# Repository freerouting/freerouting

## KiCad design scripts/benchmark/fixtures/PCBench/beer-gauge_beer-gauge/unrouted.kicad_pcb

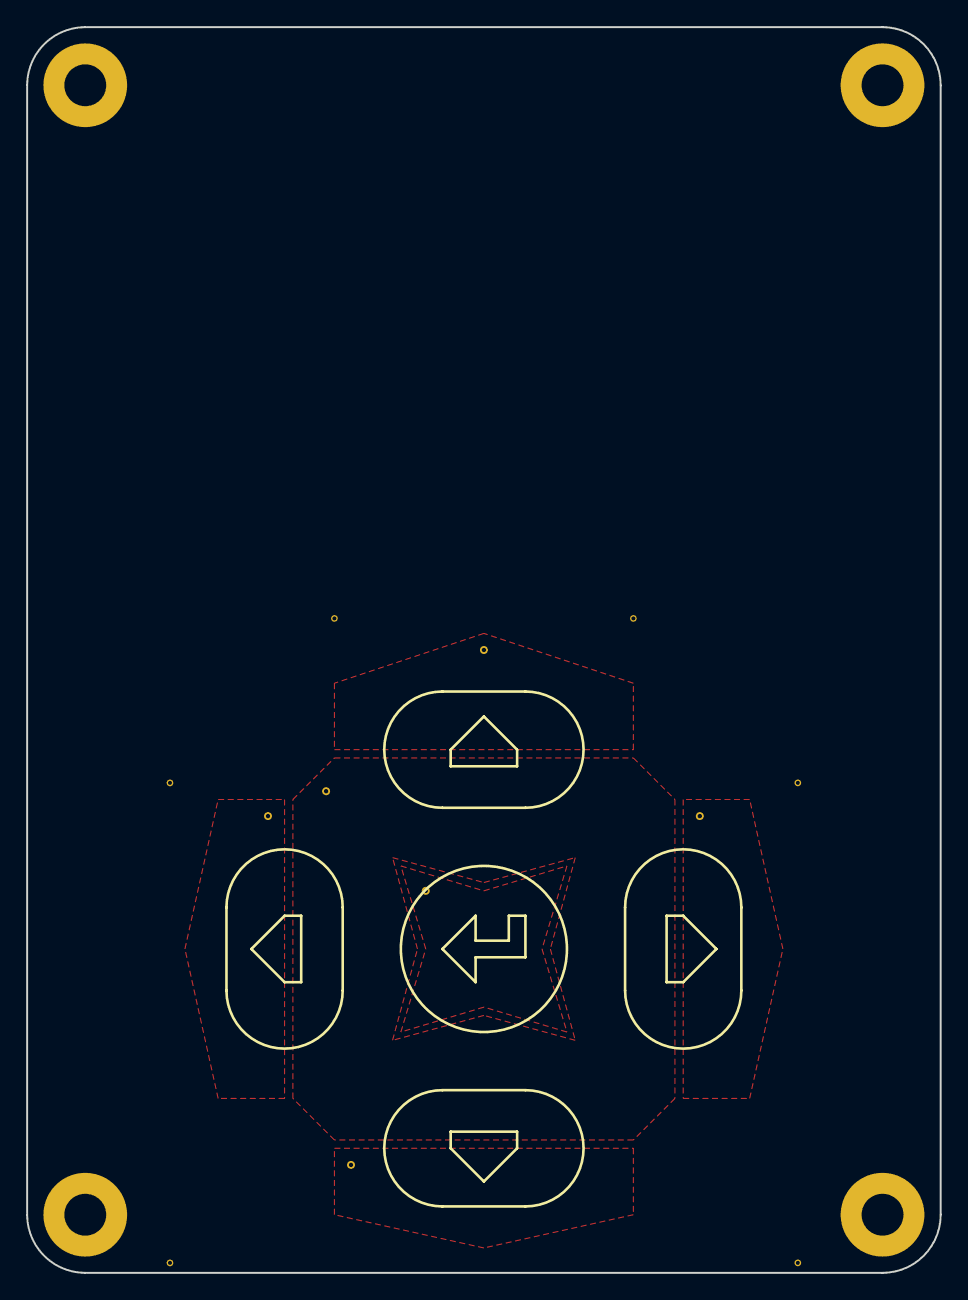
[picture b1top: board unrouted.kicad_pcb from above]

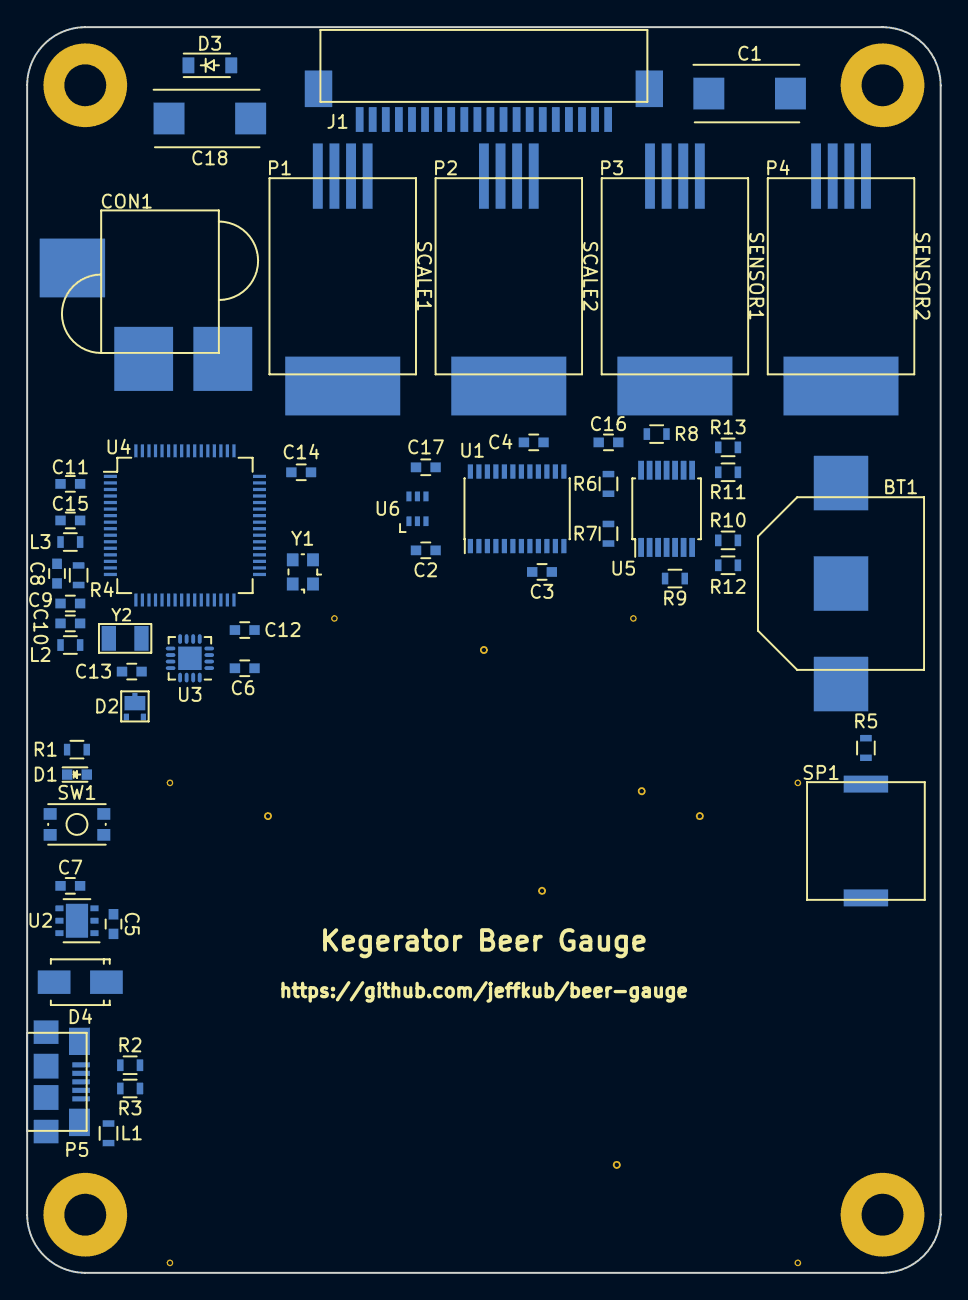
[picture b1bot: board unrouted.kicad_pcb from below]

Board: 4 copper layers, 69.8 x 95.2 mm, 62 parts (56 on the bottom side), 64 nets, no tracks yet.

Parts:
BT1: Battery; BK-885
C1: 220u; TantalC_SizeD_EIA-7343_Reflow
C2, C3, C4, C6, C9, C10, C11, C12, C13, C14, C16, C17: 0.1u; C_0603
C5, C7, C8, C15: 2.2u; C_0603
C18: 100u; TantalC_SizeD_EIA-7343_Reflow
CON1: BARREL_JACK; PJ-070AH-SMT
D1: LED; LED_0603
D2: PMEG4010CPA; SOT1061
D3: DDZ6V2B; SOD-123
D4: S1B; SMA_Standard
J1: OLED_MODULE; 0522712069
L1, L3: 600 Ohm/100 MHz; R_0603
L2: 600 Ohm/100 Mhz; R_0603
P1, P2, P3, P4: CONN_01X04; 0855135016
P5: USB_OTG; 10118192
R1, R4, R5: 470; R_0603
R2, R3: 33; R_0603
R6, R7, R8, R9, R10, R11, R12, R13: 4.7k; R_0603
SP1: PIEZO; PKMCS
SW1: SW_PUSH; SW_SPST_KMR2
U1: ADS1232; TSSOP-24_4.4x7.8mm_Pitch0.65mm
U2: LP38691; DFN-6-1EP_3x3mm_Pitch0.95mm
U3: MKL02Z32; QFN-16-1EP_3x3mm_Pitch0.5mm
U4: MK20DX256VLH7; LQFP-64_10x10mm_Pitch0.5mm
U5: TCA9543A; TSSOP-14_4.4x5mm_Pitch0.65mm
U6: SN74LVC1G58; SC-70-6
W1, W2, W3, W4, W5, W6: TEST_1P; PadVia
Y1: 16 MHz; Crystal_SMD_2520_4Pads
Y2: 32.768 kHz; ABS07

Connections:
+3V3: C1.1, C2.1, C6.1, C7.1, C11.1, C12.1, C14.1, C15.1, C16.1, C17.1, D2.2, J1.2, L3.1, R6.1, R7.1, R8.1, R9.1, R10.1, R11.1, R12.1, R13.1, U1.1, U2.4, U2.5, U3.1, U4.3, U4.7, U4.30, U4.48, U5.14, U6.5
+5V: C4.1, C5.1, C18.1, CON1.1, D3.1, D4.1, P1.1, P2.1, P3.1, P4.1, U1.16, U1.18, U2.1, U2.6
/Teensy/0: U1.19, U4.39
/Teensy/1: U1.20, U4.40
/Teensy/2: U1.22, U4.57
/Teensy/3: U1.21, U4.28
/Teensy/4: U1.8, U4.29
/Teensy/5: U1.7, U4.64
/Teensy/6: R5.2, U4.61
/Teensy/7: U4.59, U6.1
/Teensy/8: J1.16, U4.60
/Teensy/9: J1.4, U4.46
/Teensy/10: J1.15, U4.49
/Teensy/11: J1.8, U4.51
/Teensy/12: U1.24, U4.52
/Teensy/13: J1.7, U4.50, U6.6
/Teensy/15/A1: U4.43, W1.1
/Teensy/16/A2: U4.35, W2.1
/Teensy/17/A3: U4.36, W5.1
/Teensy/18/A4: R6.2, U4.38, U5.13
/Teensy/19/A5: R7.2, U4.37, U5.12
/Teensy/20/A6: R1.1, U4.62
/Teensy/21/A7: U4.63, U5.3
/Teensy/22/A8: U4.44, W3.1
/Teensy/23/A9: U4.45, W4.1
/Teensy/25: U4.42, W6.1
/Teensy/AREF: C9.1, R4.1, U4.14
/Teensy/ID: P5.4, U3.6, U4.23
/Teensy/RESET_B: U3.4, U3.13, U4.34
/Teensy/SWD_CLK: U3.8, U4.22
/Teensy/SWD_DIO: U3.7, U4.25
/Teensy/USB_D+: R3.1, U4.5
/Teensy/USB_D-: R2.1, U4.6
GND: BT1.2, C1.2, C2.2, C4.2, C5.2, C6.2, C7.2, C11.2, C12.2, C13.2, C14.2, C15.2, C16.2, C17.2, C18.2, CON1.2, D1.1, D3.2, J1.1, J1.5, J1.6, J1.10, J1.11, J1.12, J1.13, J1.14, J1.20, L1.2, L2.1, P1.4, P2.4, P3.4, P4.4, P5.5, SP1.2, SW1.1, U1.2, U1.3, U1.5, U1.6, U1.15, U1.17, U2.2, U2.7, U3.2, U3.17, U4.4, U4.31, U4.47, U5.1, U5.2, U5.7, U6.2, U6.3
unnamed: BT1.1, D2.1
unnamed: C3.1, U1.9
unnamed: C3.2, U1.10
unnamed: C8.1, L3.2, R4.2, U4.13
unnamed: C10.1, U4.17
unnamed: C8.2, C9.2, C10.2, L2.2, U4.15, U4.16
unnamed: C13.1, D2.3, U4.21
unnamed: D1.2, R1.2
unnamed: D4.2, P5.1
unnamed: L1.1, P5.6
unnamed: P1.2, U1.11
unnamed: P1.3, U1.12
unnamed: P2.2, U1.14
unnamed: P2.3, U1.13
unnamed: P3.2, R12.2, U5.6
unnamed: P3.3, R10.2, U5.5
unnamed: P4.2, R13.2, U5.10
unnamed: P4.3, R11.2, U5.9
unnamed: P5.2, R2.2
unnamed: P5.3, R3.2
unnamed: R5.1, SP1.1
unnamed: R8.2, U5.11
unnamed: R9.2, U5.4, U5.8
unnamed: SW1.2, U3.10
unnamed: U1.23, U6.4
unnamed: U3.9, U4.24
unnamed: U4.19, Y2.1
unnamed: U4.20, Y2.2
unnamed: U4.32, Y1.1
unnamed: U4.33, Y1.2

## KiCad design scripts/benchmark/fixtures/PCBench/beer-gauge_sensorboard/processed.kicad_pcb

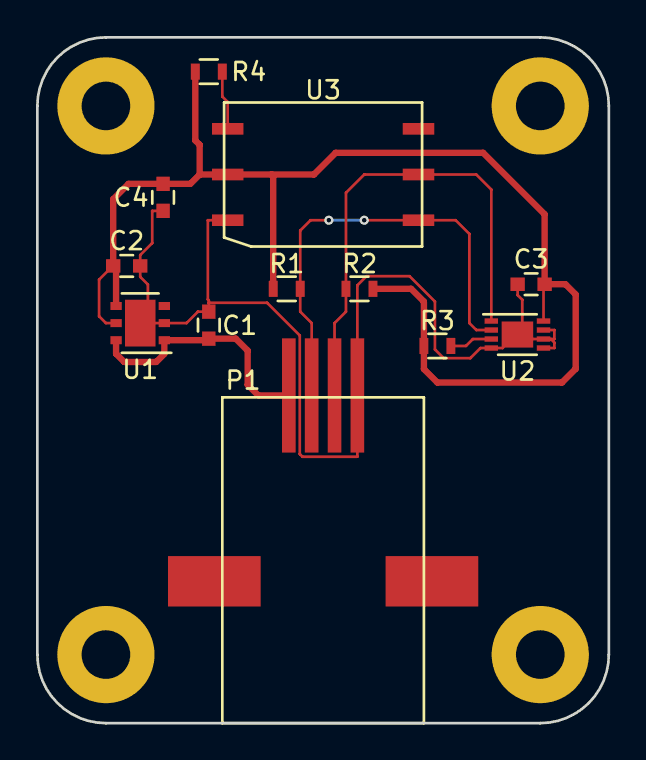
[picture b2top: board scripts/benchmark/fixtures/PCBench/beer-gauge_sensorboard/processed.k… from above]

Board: 2 copper layers, 31.8 x 38.1 mm, 12 parts (0 on the bottom side), 7 nets.

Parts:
C1, C2: 2.2u; C_0603
C3, C4: 0.1u; C_0603
P1: CONN_01X04; 0855025005
R1, R2: DNP; R_0603
R3, R4: 4.7k; R_0603
U1: LP38691; DFN-6-1EP_3x3mm_Pitch0.95mm
U2: MCP9808; DFN-8-1EP_3x2mm_Pitch0.5mm
U3: ABPMANN030PG2A3

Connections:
+3V3: C2.1, C3.1, C4.1, R1.1, R2.1, R3.1, R4.1, U1.4, U1.5, U2.8, U3.2
+5V: C1.1, P1.1, U1.1, U1.6
/I2C_SCL: P1.2, R1.2, U2.2, U3.6
/I2C_SDA: P1.3, R2.2, U2.1, U3.5
GND: C1.2, C2.2, C3.2, C4.2, P1.4, U1.2, U1.7, U2.4, U2.5, U2.6, U2.7, U2.9, U3.1
unnamed: R3.2, U2.3
unnamed: R4.2, U3.3

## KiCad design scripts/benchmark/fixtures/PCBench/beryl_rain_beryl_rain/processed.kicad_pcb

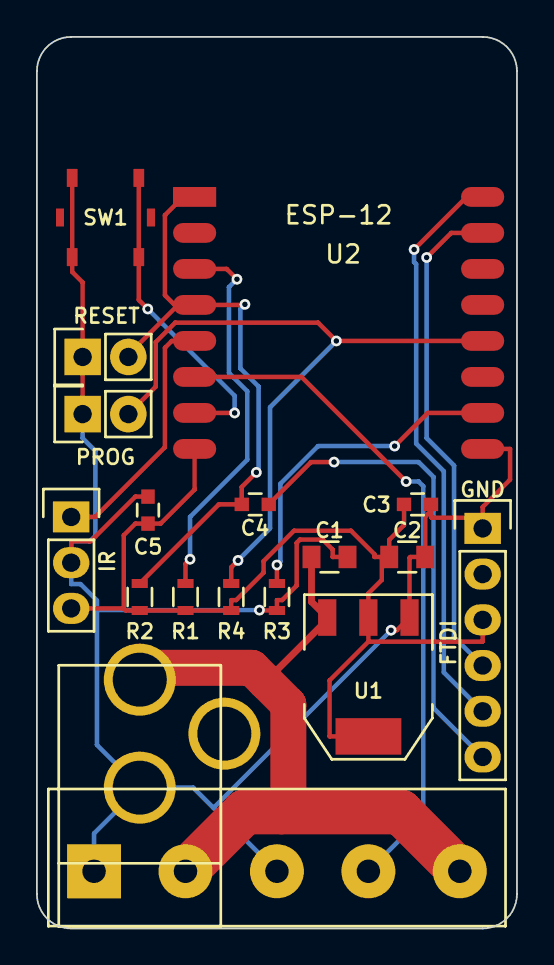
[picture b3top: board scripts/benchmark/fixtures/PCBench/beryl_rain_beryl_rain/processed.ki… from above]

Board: 2 copper layers, 26.7 x 49.5 mm, 18 parts (0 on the bottom side), 13 nets.

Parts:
C1, C2: CP; C_0805
C3, C4, C5: 0.1uF; C_0603
CON1: POWER; BARREL_JACK
P1: POWER; Terminal_Block_5.08mm_x5
P2: FTDI; Pin_Header_Straight_1x06
P3: IR; Pin_Header_Straight_1x03
P4: RESET; Pin_Header_Straight_1x02
P5: PROG; Pin_Header_Straight_1x02
R1, R2, R3, R4: 10K; R_0603
SW1: SWITCH; EVQPT5
U1: NCP1117ST33T3G; SOT-223
U2: ESP-12

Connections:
+3V3: C2.1, C3.1, C5.1, P2.3, P3.3, R1.1, R2.1, R4.1, U1.2, U1.4, U2.8
+5V: C1.1, CON1.1, P1.2, P1.5, U1.3
GND: C1.2, C2.2, C3.2, C5.2, CON1.2, P1.1, P1.3, P2.1, P3.2, P4.1, P5.1, R3.2, SW1.1, U1.1, U2.9
IR_DATA: P3.1, U2.5
LED_DATA: P1.4, U2.6
unnamed: C4.1, P2.6
unnamed: P5.2, R4.2, U2.12
unnamed: R1.2, U2.3
unnamed: R3.1, U2.10
unnamed: SW1.2, U2.7
RESET: C4.2, P4.2, R2.2, U2.1, U2.4
RX: P2.4, U2.15
TX: P2.5, U2.16

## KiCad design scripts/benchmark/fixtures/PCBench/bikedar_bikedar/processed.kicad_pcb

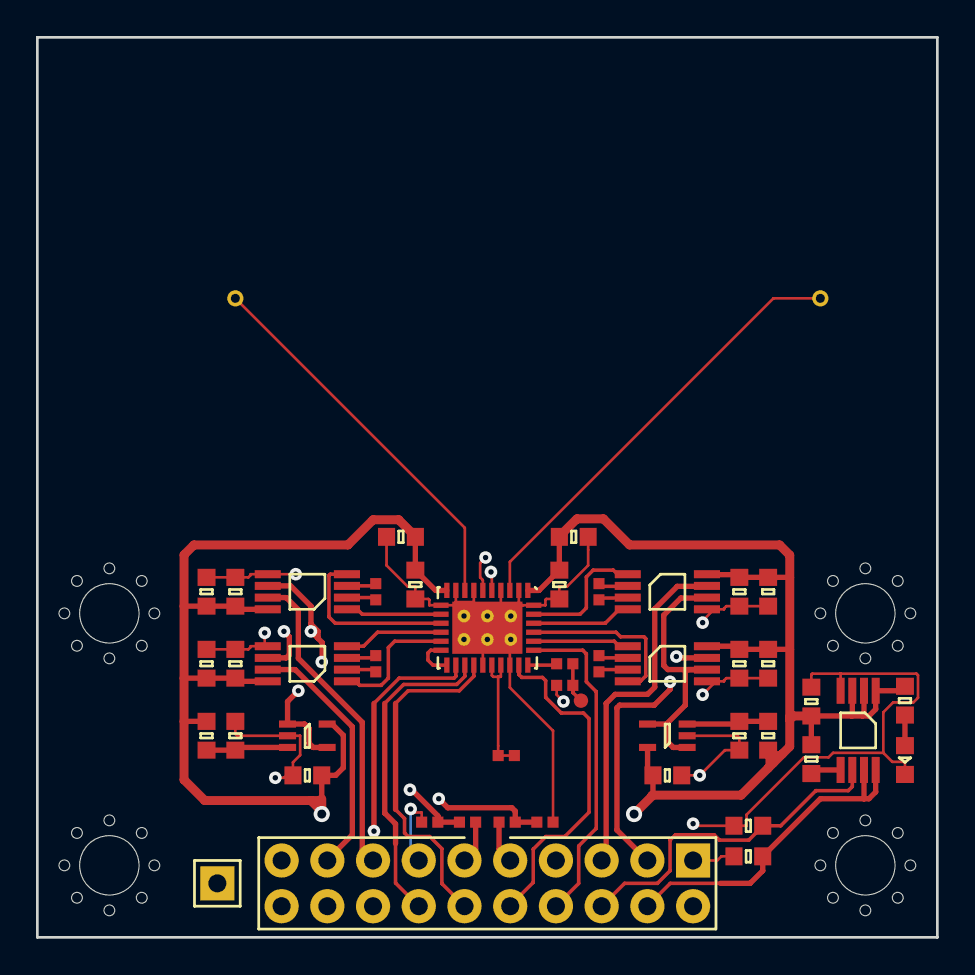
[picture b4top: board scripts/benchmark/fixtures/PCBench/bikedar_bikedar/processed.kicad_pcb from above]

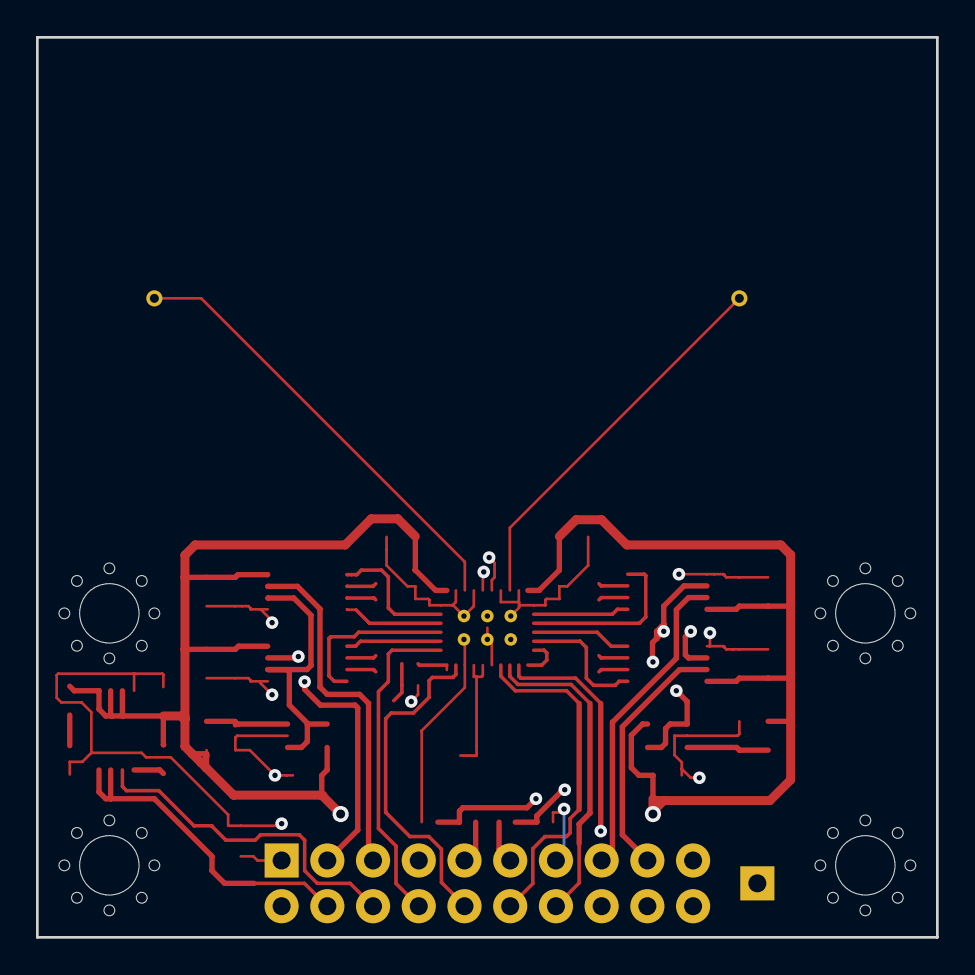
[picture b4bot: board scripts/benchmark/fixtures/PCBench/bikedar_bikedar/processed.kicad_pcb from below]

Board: 4 copper layers, 50.0 x 50.0 mm, 52 parts (2 on the bottom side), 45 nets.

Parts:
AE2, AE3: X0
C1, C3, C7, C18: 1µ; 0603
C2: 1n; 0603
C4, C15, C19, C20: 10µ; 0603
C5, C6: 100n; 0402
C8, C10, C11, C12, C13, C14, C16, C17: 100n; 0603
C9: 1n; 0402
D1: LED; 0603-LED
IC1: ADP3335; MSOP-8
IC2: BGT24MTR12; QFN-32-BGT24MTR
IC3, IC8: AD8541; SC-70-5
IC4, IC5, IC6, IC7: AD8226; MSOP-8
J1: CONN_02x10; DIL-254P-20
R1, R2, R13: 100; 0402
R3: 50; 0402
R4, R5, R10, R11, R12: 10k; 0603
R6, R7, R8, R9: 5k49; 0402
R14: 1k; 0603
TP1: TESTPAD
TP2: TESTPAD; SIL-254P-01
X1, X2, X3, X4: M3_MOUNT

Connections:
3v3: C2.2, C3.1, C4.1, C7.1, C8.1, C10.1, C11.1, C12.1, C13.1, C14.1, C15.1, C16.1, C17.1, C18.1, C19.1, C20.1, IC1.1, IC1.2, IC1.3, IC2.1, IC2.10, IC3.5, IC4.8, IC5.8, IC6.8, IC7.8, IC8.5, R4.1, R11.1, R14.1
/ANA: IC2.25, J1.10
/CLK: IC2.19, J1.14
/COARSE: J1.11, R2.1
/FINE: J1.9, R1.1
/FREQ: IC2.27, J1.8
/IFI1: IC4.7, J1.3
/IFI1_N: IC2.28, IC4.1
/IFI1_P: IC2.29, IC4.4
/IFI2: IC6.7, J1.17
/IFI2_N: IC2.15, IC6.1
/IFI2_P: IC2.14, IC6.4
/IFQ1: IC5.7, J1.5
/IFQ1_N: IC2.31, IC5.1
/IFQ1_P: IC2.30, IC5.4
/IFQ2: IC7.7, J1.15
/IFQ2_N: IC2.12, IC7.1
/IFQ2_P: IC2.13, IC7.4
/RX1: AE2.1, IC2.3
/RX2: AE3.1, IC2.8
/SI: IC2.20, J1.12
/TX: IC2.22, IC2.23, R13.1, R13.2
/VREF1: IC3.1, IC3.4, IC4.6, IC5.6
/VREF2: IC6.6, IC7.6, IC8.1, IC8.4
/~CS: IC2.18, J1.16
/~SD: IC1.6, J1.6, R10.1
GND: C1.2, C3.2, C4.2, C5.2, C6.1, C7.2, C8.2, C10.2, C11.2, C12.2, C13.2, C14.2, C15.2, C16.2, C17.2, C18.2, C19.2, C20.2, D1.1, IC1.4, IC2.2, IC2.4, IC2.7, IC2.9, IC2.11, IC2.21, IC2.24, IC2.32, IC2.EP, IC3.2, IC4.5, IC5.5, IC6.5, IC7.5, IC8.2, J1.1, J1.2, J1.7, J1.13, J1.18, J1.19, J1.20, R3.1, R5.2, R10.2, R12.2, TP2.1
unnamed: C2.1, IC1.5
unnamed: C5.1, IC2.5, R1.2
unnamed: C6.2, IC2.6, R2.2
unnamed: C9.1, R3.2, TP1.1
unnamed: C9.2, IC2.26
unnamed: D1.2, R14.2
unnamed: IC2.16, IC2.17
unnamed: IC3.3, R4.2, R5.1
unnamed: IC4.2, R6.2
unnamed: IC4.3, R6.1
unnamed: IC5.2, R7.2
unnamed: IC5.3, R7.1
unnamed: IC6.2, R8.2
unnamed: IC6.3, R8.1
unnamed: IC7.2, R9.2
unnamed: IC7.3, R9.1
unnamed: IC8.3, R11.2, R12.1
VBATT: C1.1, IC1.7, IC1.8, J1.4
